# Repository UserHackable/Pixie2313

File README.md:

## Pixie 2313 / 4313

A very bare minimum breakout for an ATtiny2313 to provide the AVR ICSP programming header to the micro controller. 

## Pixie2313 

### Board dimensions

* (140000, 80000) original units
* (1.4000, 0.8000) inches
* (35.5600, 20.3200) mm

| Front | Back |
| --- | --- |
|  |  |

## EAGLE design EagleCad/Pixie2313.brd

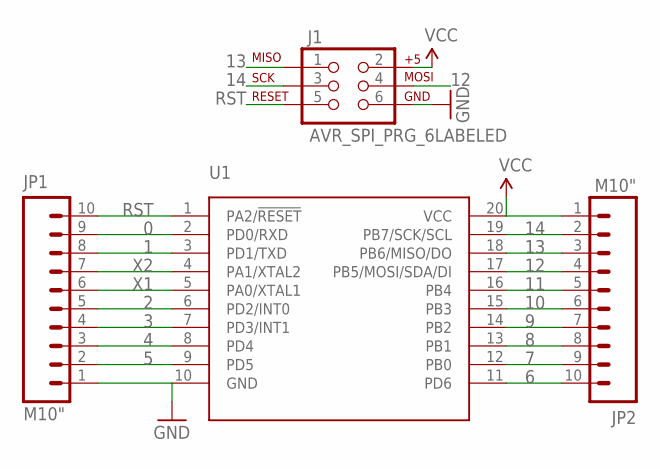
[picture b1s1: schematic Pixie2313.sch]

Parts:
J1: AVR_SPI_PRG_6LABELED; 2X3-NS
JP1, JP2: M10"; 1X10
U1: ATTINY2313APTH; DIL20

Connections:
0: JP1.9, U1.2 (PD0/RXD)
1: JP1.8, U1.3 (PD1/TXD)
2: JP1.5, U1.6 (PD2/INT0)
3: JP1.4, U1.7 (PD3/INT1)
4: JP1.3, U1.8 (PD4)
5: JP1.2, U1.9 (PD5)
6: JP2.10, U1.11 (PD6)
7: JP2.9, U1.12 (PB0)
8: JP2.8, U1.13 (PB1)
9: JP2.7, U1.14 (PB2)
10: JP2.6, U1.15 (PB3)
11: JP2.5, U1.16 (PB4)
12: J1.4, JP2.4, U1.17 (PB5/MOSI/SDA/DI)
13: J1.1, JP2.3, U1.18 (PB6/MISO/DO)
14: J1.3, JP2.2, U1.19 (PB7/SCK/SCL)
GND: J1.6, JP1.1, U1.10 (GND)
RST: J1.5, JP1.10, U1.1 (PA2/!RESET)
VCC: J1.2, JP2.1, U1.20 (VCC)
X1: JP1.6, U1.5 (PA0/XTAL1)
X2: JP1.7, U1.4 (PA1/XTAL2)

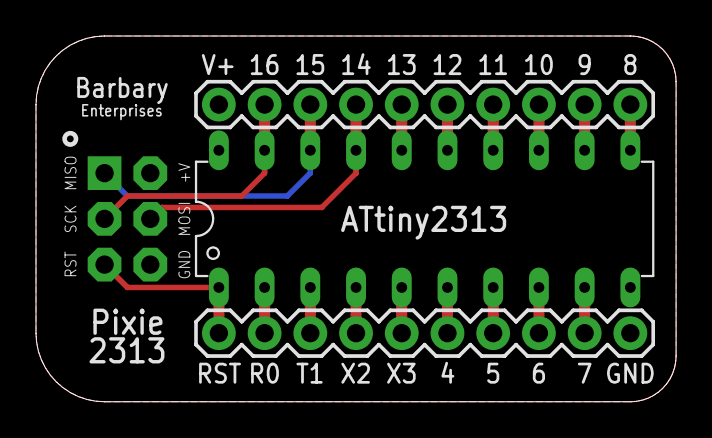
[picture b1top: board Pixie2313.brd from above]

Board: 2 copper layers, 35.6 x 20.3 mm, 4 parts (0 on the bottom side), 20 nets.

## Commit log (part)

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2016-04-08 from Makefile

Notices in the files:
parts and their libraries:
SparkFun-DigitalIC: Licensing: Creative Commons ShareAlike 4.0 International - https://creativecommons.org/licenses/by-sa/4.0
